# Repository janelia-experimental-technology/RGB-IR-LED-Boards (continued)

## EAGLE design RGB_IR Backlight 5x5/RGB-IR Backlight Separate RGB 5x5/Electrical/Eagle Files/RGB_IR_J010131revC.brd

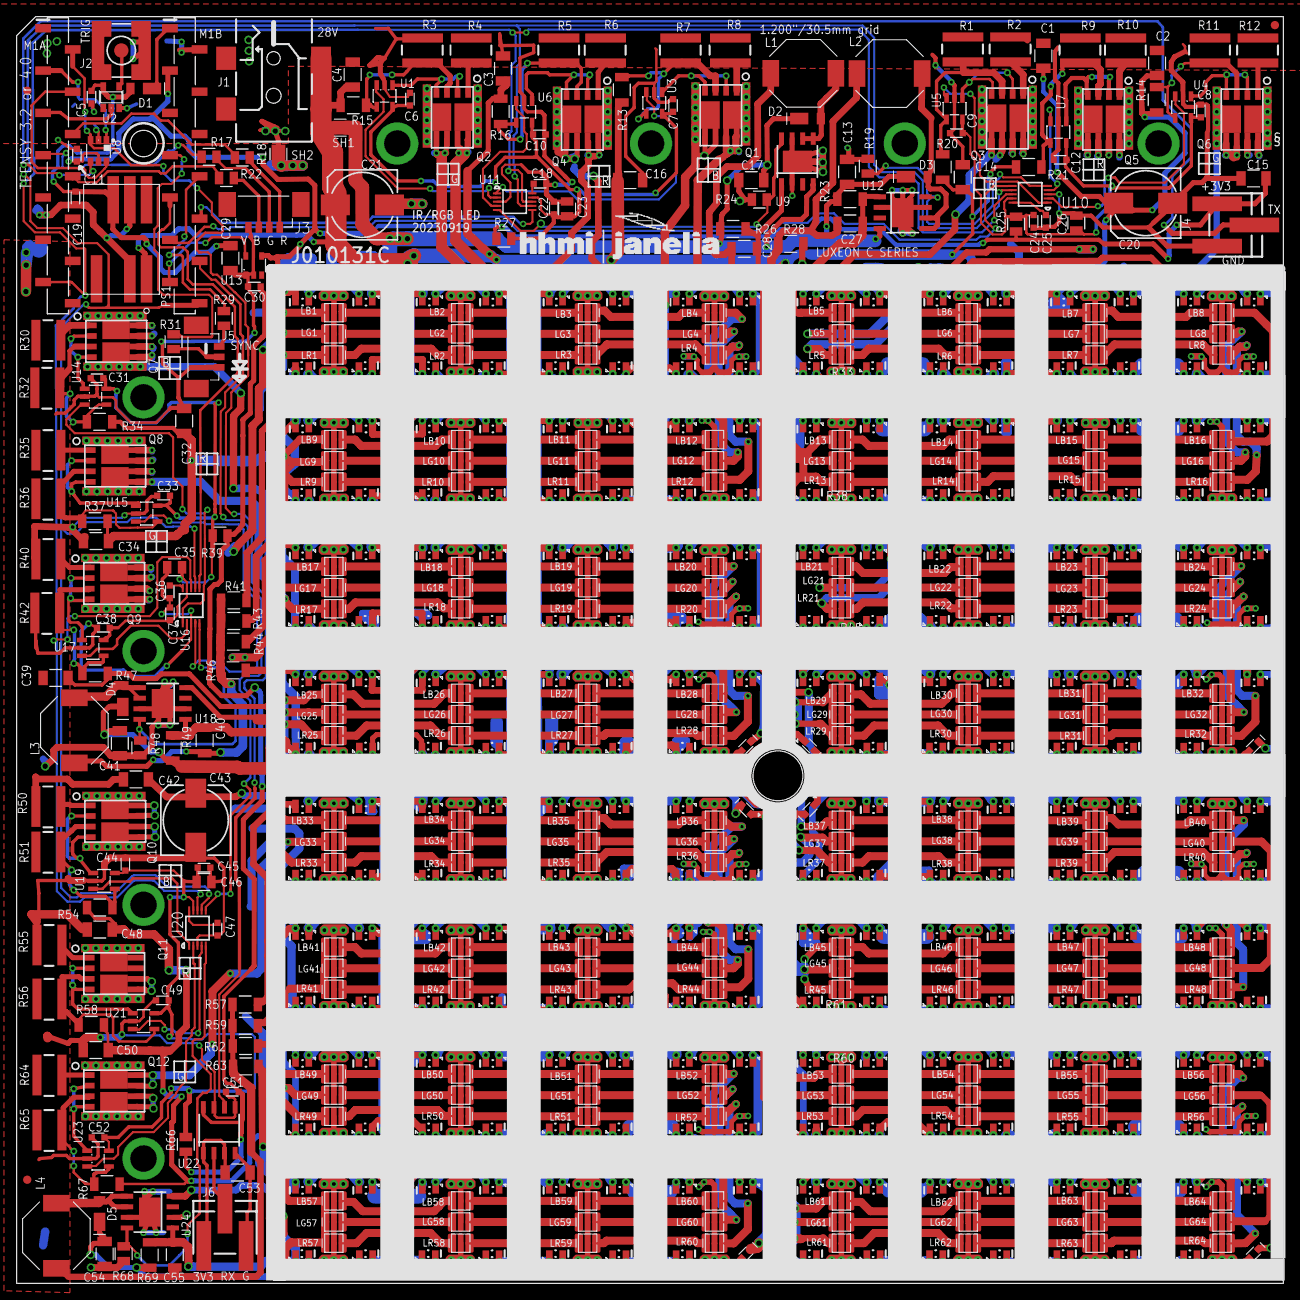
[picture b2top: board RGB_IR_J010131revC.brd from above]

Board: 2 copper layers, 152.1 x 152.1 mm, 696 parts (0 on the bottom side), 617 nets.

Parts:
C1, C2, C3, C4, C13, C14, C16, C17, C32, C34, C39, C41, C42, C48, C50, C54: 10@50; 1210S
C5, C6, C7, C8, C9, C10, C11, C12, C18, C19, C22, C24, C25, C30, C31, C33, C36, C37, C38, C44, C45, C47, C49, C51, C52: 0.1; 0603S
C15, C29, C53: 10; 1210S
C20, C21, C43: 153CLV-0810
C23, C26, C35, C46: 4.7; 0805S
C27, C28, C40, C55: 2.2@50; 1206S
D1, D2, D3, D4, D5: DLFS240L; PWRDI-123
FID1, FID2, FID3, FID4: FIDUCIAL; FIDUCIAL_1MM
IR1, IR129, IR154: SFH4050; LED_SFH4045_HEAT_A
IR2, IR3, IR4, IR5, IR6, IR7, IR8, IR9, IR10, IR11, IR12, IR13, IR14, IR15, IR16, IR17, IR18, IR19, IR20, IR21, IR22, IR23, IR24, IR25, IR26, IR27, IR28, IR29, IR30, IR31, IR32, IR33, IR34, IR35, IR36, IR37, IR38, IR39, IR40, IR41, IR42, IR43, IR44, IR45, IR46, IR47, IR48, IR49, IR50, IR51, IR52, IR53, IR54, IR55, IR56, IR57, IR58, IR59, IR60, IR61, IR62, IR63, IR64, IR65, IR66, IR67, IR68, IR69, IR70, IR71, IR72, IR73, IR74, IR75, IR76, IR77, IR78, IR79, IR80, IR81, IR82, IR83, IR84, IR85, IR86, IR87, IR88, IR89, IR90, IR91, IR92, IR93, IR94, IR95, IR96, IR97, IR98, IR99, IR100, IR101, IR102, IR103, IR104, IR105, IR107, IR108, IR109, IR110, IR111, IR112, IR113, IR114, IR115, IR116, IR118, IR119, IR120, IR121, IR122, IR123, IR125, IR126, IR127, IR130, IR131, IR132, IR133, IR134, IR135, IR138, IR139, IR140, IR141, IR142, IR143, IR144, IR145, IR146, IR147, IR148, IR149, IR150, IR151, IR152, IR153, IR155, IR156, IR157, IR158, IR159, IR160, IR161, IR162, IR163, IR164, IR165, IR166, IR167, IR168, IR169, IR170, IR171, IR172, IR173, IR174, IR175, IR176, IR177, IR178, IR179, IR180, IR181, IR182, IR183, IR184, IR185, IR186, IR187, IR188, IR189, IR190, IR191, IR192, IR193, IR194, IR195, IR196, IR197, IR198, IR199, IR200, IR201, IR202, IR203, IR204, IR205, IR206, IR207, IR208, IR209, IR210, IR211, IR212, IR213, IR214, IR215, IR216, IR217, IR218, IR219, IR220, IR221, IR222, IR223, IR224, IR225, IR226, IR227, IR228, IR229, IR230, IR231, IR232, IR233, IR234, IR235, IR236, IR237, IR238, IR239, IR240, IR241, IR242, IR243, IR244, IR245, IR246, IR247, IR248, IR249, IR250, IR251, IR253, IR254, IR255: SFH4050; LED_SFH4050_HEAT
IR106: SFH4050; LED_SFH4050_HEAT_C
IR117, IR124, IR128, IR136, IR137, IR252, IR256: SFH4050; LED_SFH4050
J1: PJ-002
J2: SMA-SMD
J3: MOLEX_1.25-4
J4, J6: TE-3-SM-V
J5: MOLEX_1.25-3
L1, L2, L3, L4: 68uH/1A; SRU8043
LB1, LB2, LB3, LB4, LB5, LB6, LB7, LB8, LB9, LB10, LB11, LB12, LB13, LB14, LB15, LB16, LB17, LB18, LB19, LB20, LB21, LB22, LB23, LB24, LB25, LB26, LB27, LB28, LB29, LB30, LB31, LB32, LB33, LB34, LB35, LB36, LB37, LB38, LB39, LB40, LB41, LB42, LB43, LB44, LB45, LB46, LB47, LB48, LB49, LB50, LB51, LB52, LB53, LB54, LB55, LB56, LB57, LB58, LB59, LB60, LB61, LB62, LB63, LB64: LED-B; SUNPLUS-LED
LG1, LG2, LG3, LG4, LG5, LG6, LG7, LG8, LG9, LG10, LG11, LG12, LG13, LG14, LG15, LG16, LG17, LG18, LG19, LG20, LG21, LG22, LG23, LG24, LG25, LG26, LG27, LG28, LG29, LG30, LG31, LG32, LG33, LG34, LG35, LG36, LG37, LG38, LG39, LG40, LG41, LG42, LG43, LG44, LG45, LG46, LG47, LG48, LG49, LG50, LG51, LG52, LG53, LG54, LG55, LG56, LG57, LG58, LG59, LG60, LG61, LG62, LG63, LG64: LED-G; SUNPLUS-LED
LR1, LR2, LR3, LR4, LR5, LR6, LR7, LR8, LR9, LR10, LR11, LR12, LR13, LR14, LR15, LR16, LR17, LR18, LR19, LR20, LR21, LR22, LR23, LR24, LR25, LR26, LR27, LR28, LR29, LR30, LR31, LR32, LR33, LR34, LR35, LR36, LR37, LR38, LR39, LR40, LR41, LR42, LR43, LR44, LR45, LR46, LR47, LR48, LR49, LR50, LR51, LR52, LR53, LR54, LR55, LR56, LR57, LR58, LR59, LR60, LR61, LR62, LR63, LR64: LED-R; SUNPLUS-LED
M1A, M1B: SSM-114-S-SV; SAMTEC_SSM-114-S-SV
PS1: DC-DC-TDN-5W
Q1, Q2, Q3, Q4, Q5, Q6, Q7, Q8, Q9, Q10, Q11, Q12: NPN_DUALLFPAK56_BIGHS; LFPAK56_HS2
R1, R2, R3, R4, R5, R6, R7, R8, R9, R10, R11, R12, R30, R32, R35, R36, R40, R42, R50, R51, R55, R56, R64, R65: 4R99; 1812
R13, R14, R15, R16, R20, R21, R34, R37, R47, R54, R58, R67: 49K9; 1206S
R17, R18, R22, R31: 332; 0805S
R19, R24, R48, R68: 4.99K; 0805S
R23, R26, R49, R69: 1R00; 1206S
R25, R27, R39, R66: 4R99; 0805S
R28, R33, R38, R41, R43, R44, R45, R46, R52, R53, R57, R59, R60, R61, R62, R63: 10R0; 1206S
R29: 100; 0805S
SH1, SH2: JUMPER
U1, U3, U4, U5, U6, U7, U14, U15, U17, U19, U21, U23: OPA237; SOT23-5
U2: 74AUC1G17DBV; SOT23-5
U8: 741G3157DBVR; DBV_R-PDSO-G6
U9, U12, U18, U24: AP8802; SOIC8-EP
U10, U11, U16, U20: AD5624R-3; MSOP10
U13: LM26; SOT23-5
U22: ADUM1100; SOIC8
V1, V2, V3, V10, V11: HS; SUNPLUS-VIAS-ONLY
V4, V12: HS; SUNPLUS-TOP-VIAS-ONLY
V5, V6, V7, V9, V13, V14, V15, V17, V18, V19, V21, V22, V23, V25, V26, V27, V29, V30, V31, V33, V34, V35, V37, V38, V39, V41, V42, V43, V45, V46, V47, V49, V50, V51, V53, V54, V55, V57, V58, V59, V61, V62, V63: SUNPLUS-VIAS-ONLY
V8, V16, V20, V24, V28, V32, V36, V40, V44, V48, V52, V56, V60, V64: SUNPLUS-VIAS-ONLYTOPVIAS; SUNPLUS-TOP-VIAS-ONLY

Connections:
3V3I: C53.1, J6.P$3, U22.1, U22.3
3V3LL: C44.1, C45.1, C46.1, C49.1, C52.1, R66.2, U19.5, U20.9, U21.5, U23.5
3V3LR: C6.1, C7.1, C10.1, C22.1, C23.1, R27.2, U1.5, U3.5, U6.5, U11.9
3V3UR: C8.1, C9.1, C12.1, C24.1, C26.1, R25.2, U4.5, U5.5, U7.5, U10.9
+3V3A: C11.1, C15.2, C30.1, C51.1, J4.P$3, M1B.3, R25.1, R27.1, R39.1, R66.1, U8.5, U13.4, U22.8
+3V3UL: C31.1, C33.1, C35.1, C37.1, C38.1, R39.2, U14.5, U15.5, U16.9, U17.5
B1A: LB53.GC, Q1.5, Q1.5A, Q1.5A1, Q1.5B, Q1.5C, Q1.5C1, Q1.5C2, Q1.6, Q1.56, Q1.56A, Q1.56B
B1B: LB37.GC, Q1.7, Q1.8, Q1.8A, Q1.8B, Q1.8C, Q1.8C1, Q1.8C2, Q1.8C3, Q1.78, Q1.78A, Q1.78B
BLLA: LB49.GC, Q10.5, Q10.5A, Q10.5A1, Q10.5B, Q10.5C, Q10.5C1, Q10.5C2, Q10.6, Q10.56, Q10.56A, Q10.56B
BLLB: LB33.GC, Q10.7, Q10.8, Q10.8A, Q10.8B, Q10.8C, Q10.8C1, Q10.8C2, Q10.8C3, Q10.78, Q10.78A, Q10.78B
BLU: M1A.8, R22.2
BLU_LL: U19.3, U20.1
BLU_LR: U3.3, U11.1
BLU_UL: U14.3, U16.1
BLU_UR: U5.3, U10.1
BULA: LB17.GC, Q7.5, Q7.5A, Q7.5A1, Q7.5B, Q7.5C, Q7.5C1, Q7.5C2, Q7.6, Q7.56, Q7.56A, Q7.56B
BULB: LB1.GC, Q7.7, Q7.8, Q7.8A, Q7.8B, Q7.8C, Q7.8C1, Q7.8C2, Q7.8C3, Q7.78, Q7.78A, Q7.78B
DIR: M1A.4, U8.6
G1A: LG53.GC, Q2.5, Q2.5A, Q2.5A1, Q2.5B, Q2.5C, Q2.5C1, Q2.5C2, Q2.6, Q2.56, Q2.56A, Q2.56B
G1B: LG37.GC, Q2.7, Q2.8, Q2.8A, Q2.8B, Q2.8C, Q2.8C1, Q2.8C2, Q2.8C3, Q2.78, Q2.78A, Q2.78B
GLLA: LG49.GC, Q12.5, Q12.5A, Q12.5A1, Q12.5B, Q12.5C, Q12.5C1, Q12.5C2, Q12.6, Q12.56, Q12.56A, Q12.56B
GLLB: LG33.GC, Q12.7, Q12.8, Q12.8A, Q12.8B, Q12.8C, Q12.8C1, Q12.8C2, Q12.8C3, Q12.78, Q12.78A, Q12.78B
GNDI: C53.2, J6.P$1, U22.4
GRN: M1A.7, R17.2
GRN_LL: U20.2, U23.3
GRN_LR: U1.3, U11.2
GRN_UL: U16.2, U17.3
GRN_UR: U4.3, U10.2
GULA_1: LG17.GC, Q9.5, Q9.5A, Q9.5A1, Q9.5B, Q9.5C, Q9.5C1, Q9.5C2, Q9.6, Q9.56, Q9.56A, Q9.56B
GULB_A: LG1.GC, Q9.7, Q9.8, Q9.8A, Q9.8B, Q9.8C, Q9.8C1, Q9.8C2, Q9.8C3, Q9.78, Q9.78A, Q9.78B
IGND: C13.2, C17.2, C21.-, C41.2, C54.2, R19.1, R24.1, R48.1, R68.1, SH2.2, U9.2, U9.7, U9.EP, U12.2, U12.7, U12.EP, U18.2, U18.7, U18.EP, U24.2, U24.7, U24.EP
IR_DRV_LL: C55.1, IR145.A, IR145.A1, IR177.A, IR177.A1, IR209.A, IR209.A1, IR241.A, IR241.A1, R69.1, U24.1
IR_DRV_LR: C28.1, IR153.A, IR153.A1, IR185.A, IR185.A1, IR217.A, IR217.A1, IR245.A, IR245.A1, R26.1, U9.1
IR_DRV_UL: C40.1, IR17.A, IR17.A1, IR49.A, IR49.A1, IR81.A, IR81.A1, IR113.A, IR113.A1, R49.1, U18.1
IR_DRV_UR: C27.1, IR25.A, IR25.A1, IR57.A, IR57.A1, IR89.A, IR89.A1, IR117.A, R23.1, U12.1
IR_LL: R68.2, U20.5, U24.8
IR_LR: R24.2, U9.8, U11.5
IR_RET_UL: C40.2, L3.1, R41.2, R43.2, R44.2, R46.2
IR_RET_UL1: C55.2, L4.1, R57.2, R59.2, R62.2, R63.2
IR_RET_UL2: C27.2, L2.1, R28.2, R33.2, R38.2, R45.2
IR_RET_UL3: C28.2, L1.1, R52.2, R53.2, R60.2, R61.2
IR_UL: R48.2, U16.5, U18.8
IR_UR: R19.2, U10.5, U12.8
ISO-5: C5.1, C19.1, C29.1, D1.A, PS1.7, U2.5
LED: M1B.7, R31.2
LGND: C1.2, C2.2, C3.2, C4.2, C5.2, C6.2, C7.2, C8.2, C9.2, C10.2, C11.2, C12.2, C14.2, C15.1, C16.2, C18.2, C19.2, C20.-, C22.2, C23.2, C24.2, C25.2, C26.2, C29.2, C30.2, C31.2, C32.2, C33.2, C34.2, C35.2, C36.2, C37.2, C38.2, C39.2, C42.2, C43.-, C44.2, C45.2, C46.2, C47.2, C48.2, C49.2, C50.2, C51.2, C52.2, J1.2, J2.2@1, J2.2@2, J2.2@3, J2.2@4, J2.2@5, J2.2@6, J3.4, J4.P$1, J5.3, M1A.1, M1B.2, PS1.2, PS1.6, R1.1, R2.1, R3.1, R4.1, R5.1, R6.1, R7.1, R8.1, R9.1, R10.1, R11.1, R12.1, R30.1, R32.1, R35.1, R36.1, R40.1, R42.1, R50.1, R51.1, R55.1, R56.1, R64.1, R65.1, SH2.1, U1.2, U2.3, U3.2, U4.2, U5.2, U6.2, U7.2, U8.2, U10.3, U11.3, U13.1, U13.2, U14.2, U15.2, U16.3, U17.2, U19.2, U20.3, U21.2, U22.5, U22.7, U23.2
LL_EN: M1B.12, U20.6
LR_EN: M1B.10, U11.6
MOSI: M1A.13, U10.8, U11.8, U16.8, U20.8
unnamed: IR7.A, IR7.A1, IR8.C, IR8.C1
unnamed: IR6.A, IR6.A1, IR7.C, IR7.C1
unnamed: IR71.A, IR71.A1, IR72.C, IR72.C1
unnamed: IR70.A, IR70.A1, IR71.C, IR71.C1
unnamed: IR69.A, IR69.A1, IR70.C, IR70.C1
unnamed: IR67.A, IR67.A1, IR68.C, IR68.C1
unnamed: IR66.A, IR66.A1, IR67.C, IR67.C1
unnamed: IR65.A, IR65.A1, IR66.C, IR66.C1
unnamed: IR5.A, IR5.A1, IR6.C, IR6.C1
unnamed: IR3.A, IR3.A1, IR4.C, IR4.C1
unnamed: IR2.A, IR2.A1, IR3.C, IR3.C1
unnamed: IR1.A, IR1.A1, IR2.C, IR2.C1
unnamed: IR17.C, IR17.C1, IR18.A, IR18.A1
unnamed: IR81.C, IR81.C1, IR82.A, IR82.A1
unnamed: IR18.C, IR18.C1, IR19.A, IR19.A1
unnamed: IR82.C, IR82.C1, IR83.A, IR83.A1
unnamed: IR83.C, IR83.C1, IR84.A, IR84.A1
unnamed: IR68.A, IR68.A1, IR69.C, IR69.C1
unnamed: IR103.A, IR103.A1, IR104.C, IR104.C1
unnamed: IR102.A, IR102.A1, IR103.C, IR103.C1
unnamed: IR101.A, IR101.A1, IR102.C, IR102.C1
unnamed: IR100.A, IR100.A1, IR101.C, IR101.C1
unnamed: IR99.A, IR99.A1, IR100.C, IR100.C1
unnamed: IR19.C, IR19.C1, IR20.A, IR20.A1
unnamed: IR4.A, IR4.A1, IR5.C, IR5.C1
unnamed: IR39.A, IR39.A1, IR40.C, IR40.C1
unnamed: IR38.A, IR38.A1, IR39.C, IR39.C1
unnamed: IR37.A, IR37.A1, IR38.C, IR38.C1
unnamed: IR98.A, IR98.A1, IR99.C, IR99.C1
unnamed: IR36.A, IR36.A1, IR37.C, IR37.C1
unnamed: IR35.A, IR35.A1, IR36.C, IR36.C1
unnamed: IR97.A, IR97.A1, IR98.C, IR98.C1
unnamed: IR85.C, IR85.C1, IR86.A, IR86.A1
unnamed: IR86.C, IR86.C1, IR87.A, IR87.A1
unnamed: IR34.A, IR34.A1, IR35.C, IR35.C1
unnamed: IR87.C, IR87.C1, IR88.A, IR88.A1
unnamed: IR33.A, IR33.A1, IR34.C, IR34.C1
unnamed: IR21.C, IR21.C1, IR22.A, IR22.A1
unnamed: IR22.C, IR22.C1, IR23.A, IR23.A1
unnamed: IR23.C, IR23.C1, IR24.A, IR24.A1
unnamed: IR49.C, IR49.C1, IR50.A, IR50.A1
unnamed: IR50.C, IR50.C1, IR51.A, IR51.A1
unnamed: IR51.C, IR51.C1, IR52.A, IR52.A1
unnamed: IR53.C, IR53.C1, IR54.A, IR54.A1
unnamed: IR54.C, IR54.C1, IR55.A, IR55.A1
unnamed: IR55.C, IR55.C1, IR56.A, IR56.A1
unnamed: IR113.C, IR113.C1, IR114.A, IR114.A1
unnamed: IR20.C, IR20.C1, IR21.A, IR21.A1
unnamed: IR114.C, IR114.C1, IR115.A, IR115.A1
unnamed: IR8.A, IR8.A1, IR24.C, IR24.C1
unnamed: IR52.C, IR52.C1, IR53.A, IR53.A1
unnamed: IR115.C, IR115.C1, IR121.A, IR121.A1
unnamed: IR1.C, R41.1
unnamed: IR40.A, IR40.A1, IR56.C, IR56.C1
unnamed: IR33.C, IR33.C1, R43.1
unnamed: LG9.GC, LG10.GA
unnamed: LR9.GC, LR10.GA
unnamed: IR65.C, IR65.C1, R44.1
unnamed: IR135.A, IR135.A1, IR136.C
unnamed: LB9.GC, LB10.GA
unnamed: IR116.C, IR116.C1, IR122.A, IR122.A1
unnamed: IR134.A, IR134.A1, IR135.C, IR135.C1
unnamed: LG10.GC, LG11.GA
unnamed: IR122.C, IR122.C1, IR123.A, IR123.A1
unnamed: IR123.C, IR123.C1, IR124.A
unnamed: Q8.3, R36.2, R37.1, U15.4
unnamed: D4.A, L3.2, U18.5, U18.6
unnamed: IR84.C, IR84.C1, IR85.A, IR85.A1
unnamed: LR10.GC, LR11.GA
unnamed: IR72.A, IR72.A1, IR88.C, IR88.C1
unnamed: C36.1, U16.10
unnamed: IR116.A, IR116.A1, IR121.C, IR121.C1
unnamed: LB10.GC, LB11.GA
unnamed: LG11.GC, LG12.GA
unnamed: IR104.A, IR104.A1, IR124.C
unnamed: IR133.A, IR133.A1, IR134.C, IR134.C1
unnamed: LR11.GC, LR12.GA
unnamed: IR97.C, IR97.C1, R46.1
unnamed: Q9.3, R42.2, R47.1, U17.4
unnamed: LB11.GC, LB12.GA
unnamed: LG4.GA, LG12.GC
unnamed: Q8.1, R35.2
unnamed: LR4.GA, LR12.GC
unnamed: Q8.2, Q8.4, U15.1
unnamed: LB4.GA, LB12.GC
unnamed: LB2.GA, LB3.GC
unnamed: LR2.GA, LR3.GC
unnamed: LG2.GA, LG3.GC
unnamed: LB1.GA, LB2.GC
unnamed: C47.1, U20.10
unnamed: LR1.GA, LR2.GC
unnamed: LG1.GA, LG2.GC
unnamed: LG3.GA, LG4.GC
unnamed: LR3.GA, LR4.GC
unnamed: LB3.GA, LB4.GC
unnamed: C25.1, U10.10
unnamed: Q9.2, Q9.4, U17.1
unnamed: C18.1, U11.10
unnamed: LG25.GC, LG26.GA
unnamed: LR25.GC, LR26.GA
unnamed: LB25.GC, LB26.GA
unnamed: LG26.GC, LG27.GA
unnamed: LR26.GC, LR27.GA
unnamed: LB26.GC, LB27.GA
unnamed: LG27.GC, LG28.GA
unnamed: LR27.GC, LR28.GA
unnamed: LB27.GC, LB28.GA
unnamed: LG20.GA, LG28.GC
unnamed: LR20.GA, LR28.GC
unnamed: LB20.GA, LB28.GC
unnamed: LG19.GA, LG20.GC
unnamed: LR19.GA, LR20.GC
unnamed: LB19.GA, LB20.GC
unnamed: LG18.GA, LG19.GC
unnamed: LR18.GA, LR19.GC
unnamed: LB18.GA, LB19.GC
unnamed: LG17.GA, LG18.GC
unnamed: LR17.GA, LR18.GC
unnamed: LB17.GA, LB18.GC
unnamed: Q7.2, Q7.4, U14.1
unnamed: J3.3, R22.1
unnamed: IR131.A, IR131.A1, IR132.C, IR132.C1
unnamed: Q7.1, R30.2
unnamed: J2.1, U2.4
unnamed: Q9.1, R40.2
unnamed: IR130.A, IR130.A1, IR131.C, IR131.C1
unnamed: IR129.A, IR129.A1, IR130.C, IR130.C1
unnamed: IR145.C, IR145.C1, IR146.A, IR146.A1
unnamed: IR146.C, IR146.C1, IR147.A, IR147.A1
unnamed: IR147.C, IR147.C1, IR148.A, IR148.A1
unnamed: IR132.A, IR132.A1, IR133.C, IR133.C1
unnamed: IR167.A, IR167.A1, IR168.C, IR168.C1
unnamed: IR166.A, IR166.A1, IR167.C, IR167.C1
unnamed: IR165.A, IR165.A1, IR166.C, IR166.C1
unnamed: IR164.A, IR164.A1, IR165.C, IR165.C1
unnamed: IR163.A, IR163.A1, IR164.C, IR164.C1
unnamed: IR162.A, IR162.A1, IR163.C, IR163.C1
unnamed: IR161.A, IR161.A1, IR162.C, IR162.C1
unnamed: IR149.C, IR149.C1, IR150.A, IR150.A1
unnamed: IR150.C, IR150.C1, IR151.A, IR151.A1
unnamed: IR151.C, IR151.C1, IR152.A, IR152.A1
unnamed: IR177.C, IR177.C1, IR178.A, IR178.A1
unnamed: IR178.C, IR178.C1, IR179.A, IR179.A1
unnamed: IR179.C, IR179.C1, IR180.A, IR180.A1
unnamed: IR181.C, IR181.C1, IR182.A, IR182.A1
unnamed: IR182.C, IR182.C1, IR183.A, IR183.A1
unnamed: IR183.C, IR183.C1, IR184.A, IR184.A1
unnamed: IR148.C, IR148.C1, IR149.A, IR149.A1
unnamed: IR136.A, IR152.C, IR152.C1
unnamed: IR180.C, IR180.C1, IR181.A, IR181.A1
unnamed: IR168.A, IR168.A1, IR184.C, IR184.C1
unnamed: IR129.C, R57.1
unnamed: IR161.C, IR161.C1, R59.1
unnamed: IR199.A, IR199.A1, IR200.C, IR200.C1
unnamed: IR198.A, IR198.A1, IR199.C, IR199.C1
unnamed: IR197.A, IR197.A1, IR198.C, IR198.C1
unnamed: IR195.A, IR195.A1, IR196.C, IR196.C1
unnamed: IR194.A, IR194.A1, IR195.C, IR195.C1
unnamed: IR193.A, IR193.A1, IR194.C, IR194.C1
unnamed: IR209.C, IR209.C1, IR210.A, IR210.A1
unnamed: IR210.C, IR210.C1, IR211.A, IR211.A1
unnamed: IR211.C, IR211.C1, IR212.A, IR212.A1
unnamed: IR196.A, IR196.A1, IR197.C, IR197.C1
unnamed: IR231.A, IR231.A1, IR232.C, IR232.C1
unnamed: IR230.A, IR230.A1, IR231.C, IR231.C1
unnamed: IR229.A, IR229.A1, IR230.C, IR230.C1
unnamed: IR228.A, IR228.A1, IR229.C, IR229.C1
unnamed: IR227.A, IR227.A1, IR228.C, IR228.C1
unnamed: IR226.A, IR226.A1, IR227.C, IR227.C1
unnamed: IR225.A, IR225.A1, IR226.C, IR226.C1
unnamed: IR213.C, IR213.C1, IR214.A, IR214.A1
unnamed: IR214.C, IR214.C1, IR215.A, IR215.A1
unnamed: IR215.C, IR215.C1, IR216.A, IR216.A1
unnamed: IR241.C, IR241.C1, IR242.A, IR242.A1
unnamed: IR242.C, IR242.C1, IR243.A, IR243.A1
unnamed: IR243.C, IR243.C1, IR249.A, IR249.A1
unnamed: IR244.C, IR244.C1, IR250.A, IR250.A1
unnamed: IR250.C, IR250.C1, IR251.A, IR251.A1
unnamed: IR251.C, IR251.C1, IR252.A
unnamed: IR212.C, IR212.C1, IR213.A, IR213.A1
unnamed: IR200.A, IR200.A1, IR216.C, IR216.C1
unnamed: IR244.A, IR244.A1, IR249.C, IR249.C1
unnamed: IR232.A, IR232.A1, IR252.C
unnamed: IR193.C, IR193.C1, R62.1
unnamed: IR225.C, IR225.C1, R63.1
unnamed: Q10.3, R51.2, R54.1, U19.4
unnamed: D5.A, L4.2, U24.5, U24.6
unnamed: Q11.3, R56.2, R58.1, U21.4
unnamed: Q11.2, Q11.4, U21.1
unnamed: LG41.GC, LG42.GA
unnamed: LR41.GC, LR42.GA
unnamed: LB41.GC, LB42.GA
unnamed: LG42.GC, LG43.GA
unnamed: LR42.GC, LR43.GA
unnamed: LB42.GC, LB43.GA
unnamed: LG43.GC, LG44.GA
unnamed: LR43.GC, LR44.GA
unnamed: LB43.GC, LB44.GA
unnamed: LG36.GA, LG44.GC
unnamed: LR36.GA, LR44.GC
unnamed: LG57.GC, LG58.GA
unnamed: Q7.3, R32.2, R34.1, U14.4
unnamed: LR57.GC, LR58.GA
unnamed: LB57.GC, LB58.GA
unnamed: LG58.GC, LG59.GA
unnamed: LR58.GC, LR59.GA
unnamed: LB58.GC, LB59.GA
unnamed: LG59.GC, LG60.GA
unnamed: LR59.GC, LR60.GA
unnamed: LB59.GC, LB60.GA
unnamed: LG52.GA, LG60.GC
unnamed: J3.2, R17.1
unnamed: Q12.3, R65.2, R67.1, U23.4
unnamed: Q12.2, Q12.4, U23.1
unnamed: J3.1, R18.1
unnamed: LR52.GA, LR60.GC
unnamed: LB52.GA, LB60.GC
unnamed: LB36.GA, LB44.GC
unnamed: LB33.GA, LB34.GC
unnamed: LR33.GA, LR34.GC
unnamed: LG33.GA, LG34.GC
unnamed: LB34.GA, LB35.GC
unnamed: LR34.GA, LR35.GC
unnamed: LG34.GA, LG35.GC
unnamed: LG35.GA, LG36.GC
unnamed: LR35.GA, LR36.GC
unnamed: LB35.GA, LB36.GC
unnamed: LG51.GA, LG52.GC
unnamed: LR51.GA, LR52.GC
unnamed: LB51.GA, LB52.GC
unnamed: LG50.GA, LG51.GC
unnamed: LR50.GA, LR51.GC
unnamed: LB50.GA, LB51.GC
unnamed: LG49.GA, LG50.GC
unnamed: LR49.GA, LR50.GC
unnamed: LB49.GA, LB50.GC
unnamed: Q10.2, Q10.4, U19.1
unnamed: LB9.T, LG9.T, LR9.T, V9.T1, V9.T2, V9.T3, V9.T4, V9.T5, V9.T6
unnamed: Q10.1, R50.2
unnamed: Q11.1, R55.2
unnamed: LG13.GC, LG14.GA
unnamed: LR13.GC, LR14.GA
unnamed: Q12.1, R64.2
unnamed: LG45.GC, LG46.GA
unnamed: IR15.A, IR15.A1, IR16.C, IR16.C1
unnamed: IR14.A, IR14.A1, IR15.C, IR15.C1
unnamed: IR13.A, IR13.A1, IR14.C, IR14.C1
unnamed: IR11.A, IR11.A1, IR12.C, IR12.C1
unnamed: IR10.A, IR10.A1, IR11.C, IR11.C1
unnamed: IR9.A, IR9.A1, IR10.C, IR10.C1
unnamed: IR25.C, IR25.C1, IR26.A, IR26.A1
unnamed: IR26.C, IR26.C1, IR27.A, IR27.A1
unnamed: IR27.C, IR27.C1, IR28.A, IR28.A1
unnamed: IR12.A, IR12.A1, IR13.C, IR13.C1
unnamed: IR47.A, IR47.A1, IR48.C, IR48.C1
unnamed: IR46.A, IR46.A1, IR47.C, IR47.C1
unnamed: IR45.A, IR45.A1, IR46.C, IR46.C1
unnamed: IR44.A, IR44.A1, IR45.C, IR45.C1
unnamed: IR43.A, IR43.A1, IR44.C, IR44.C1
unnamed: IR42.A, IR42.A1, IR43.C, IR43.C1
unnamed: IR41.A, IR41.A1, IR42.C, IR42.C1
unnamed: IR29.C, IR29.C1, IR30.A, IR30.A1
unnamed: IR30.C, IR30.C1, IR31.A, IR31.A1
unnamed: IR31.C, IR31.C1, IR32.A, IR32.A1
unnamed: IR57.C, IR57.C1, IR58.A, IR58.A1
unnamed: IR58.C, IR58.C1, IR59.A, IR59.A1
unnamed: IR59.C, IR59.C1, IR60.A, IR60.A1
unnamed: IR61.C, IR61.C1, IR62.A, IR62.A1
unnamed: IR62.C, IR62.C1, IR63.A, IR63.A1
unnamed: IR63.C, IR63.C1, IR64.A, IR64.A1
unnamed: IR28.C, IR28.C1, IR29.A, IR29.A1
unnamed: IR16.A, IR16.A1, IR32.C, IR32.C1
unnamed: IR60.C, IR60.C1, IR61.A, IR61.A1
unnamed: IR48.A, IR48.A1, IR64.C, IR64.C1
unnamed: IR9.C, IR9.C1, R28.1
unnamed: IR41.C, IR41.C1, R33.1
unnamed: IR79.A, IR79.A1, IR80.C, IR80.C1
unnamed: IR78.A, IR78.A1, IR79.C, IR79.C1
unnamed: IR77.A, IR77.A1, IR78.C, IR78.C1
unnamed: IR75.A, IR75.A1, IR76.C, IR76.C1
unnamed: IR74.A, IR74.A1, IR75.C, IR75.C1
unnamed: IR73.A, IR73.A1, IR74.C, IR74.C1
unnamed: IR89.C, IR89.C1, IR90.A, IR90.A1
unnamed: IR90.C, IR90.C1, IR91.A, IR91.A1
unnamed: IR91.C, IR91.C1, IR92.A, IR92.A1
unnamed: IR76.A, IR76.A1, IR77.C, IR77.C1
unnamed: IR111.A, IR111.A1, IR112.C, IR112.C1
unnamed: IR110.A, IR110.A1, IR111.C, IR111.C1
unnamed: IR109.A, IR109.A1, IR110.C, IR110.C1
unnamed: IR108.A, IR108.A1, IR109.C, IR109.C1
unnamed: IR107.A, IR107.A1, IR108.C, IR108.C1
unnamed: IR106.A, IR107.C, IR107.C1
unnamed: IR105.A, IR105.A1, IR106.C, IR106.C1
unnamed: IR93.C, IR93.C1, IR94.A, IR94.A1
unnamed: IR94.C, IR94.C1, IR95.A, IR95.A1
unnamed: IR95.C, IR95.C1, IR96.A, IR96.A1
unnamed: IR117.C, IR118.A, IR118.A1
unnamed: IR118.C, IR118.C1, IR119.A, IR119.A1
unnamed: IR119.C, IR119.C1, IR125.A, IR125.A1
unnamed: IR120.C, IR120.C1, IR126.A, IR126.A1
unnamed: IR126.C, IR126.C1, IR127.A, IR127.A1
unnamed: IR127.C, IR127.C1, IR128.A
unnamed: IR92.C, IR92.C1, IR93.A, IR93.A1
unnamed: IR80.A, IR80.A1, IR96.C, IR96.C1
unnamed: IR120.A, IR120.A1, IR125.C, IR125.C1
unnamed: IR112.A, IR112.A1, IR128.C
unnamed: IR73.C, IR73.C1, R38.1
unnamed: IR105.C, IR105.C1, R45.1
unnamed: Q6.3, R11.2, R14.1, U4.4
unnamed: D3.A, L2.2, U12.5, U12.6
unnamed: Q5.3, R9.2, R21.1, U7.4
unnamed: Q5.2, Q5.4, U7.1
unnamed: LB13.GC, LB14.GA
unnamed: LG14.GC, LG15.GA
unnamed: LR14.GC, LR15.GA
unnamed: LB14.GC, LB15.GA
unnamed: LG15.GC, LG16.GA
unnamed: LR15.GC, LR16.GA
unnamed: LB15.GC, LB16.GA
unnamed: LG8.GA, LG16.GC
unnamed: LR8.GA, LR16.GC
unnamed: LG29.GC, LG30.GA
unnamed: LR29.GC, LR30.GA
unnamed: LB10.T, LG10.T, LR10.T, V10.T1, V10.T2, V10.T3, V10.T4, V10.T5, V10.T6
unnamed: LB29.GC, LB30.GA
unnamed: LG30.GC, LG31.GA
unnamed: LR30.GC, LR31.GA
unnamed: LB30.GC, LB31.GA
unnamed: LG31.GC, LG32.GA
unnamed: LR31.GC, LR32.GA
unnamed: LB31.GC, LB32.GA
unnamed: LG24.GA, LG32.GC
unnamed: LR24.GA, LR32.GC
unnamed: LB11.T, LG11.T, LR11.T, V11.T1, V11.T2, V11.T3, V11.T4, V11.T5, V11.T6
unnamed: Q3.3, R1.2, R20.1, U5.4
unnamed: Q3.2, Q3.4, U5.1
unnamed: LB1.T, LG1.T, LR1.T, V1.T1, V1.T2, V1.T3, V1.T4, V1.T5, V1.T6
unnamed: LB24.GA, LB32.GC
unnamed: LB8.GA, LB16.GC
unnamed: LB5.GA, LB6.GC
unnamed: LR5.GA, LR6.GC
unnamed: LG5.GA, LG6.GC
unnamed: LB6.GA, LB7.GC
unnamed: LR6.GA, LR7.GC
unnamed: LG6.GA, LG7.GC
unnamed: LG7.GA, LG8.GC
unnamed: LR7.GA, LR8.GC
unnamed: LB7.GA, LB8.GC
unnamed: LG23.GA, LG24.GC
unnamed: LR23.GA, LR24.GC
unnamed: LB23.GA, LB24.GC
unnamed: LG22.GA, LG23.GC
unnamed: LR22.GA, LR23.GC
unnamed: LB22.GA, LB23.GC
unnamed: LG21.GA, LG22.GC
unnamed: LR21.GA, LR22.GC
unnamed: LB21.GA, LB22.GC
unnamed: Q6.2, Q6.4, U4.1
unnamed: LB4.T, LG4.T, LR4.T, V4.T1, V4.T2, V4.T3
unnamed: Q6.1, R12.2
unnamed: Q5.1, R10.2
unnamed: J5.2, R31.1
unnamed: LB25.T, LG25.T, LR25.T, V25.T1, V25.T2, V25.T3, V25.T4, V25.T5, V25.T6
unnamed: Q3.1, R2.2
unnamed: LB27.T, LG27.T, LR27.T, V27.T1, V27.T2, V27.T3, V27.T4, V27.T5, V27.T6
unnamed: IR143.A, IR143.A1, IR144.C, IR144.C1
unnamed: IR142.A, IR142.A1, IR143.C, IR143.C1
unnamed: IR141.A, IR141.A1, IR142.C, IR142.C1
unnamed: IR139.A, IR139.A1, IR140.C, IR140.C1
unnamed: IR138.A, IR138.A1, IR139.C, IR139.C1
unnamed: IR137.A, IR138.C, IR138.C1
unnamed: IR153.C, IR153.C1, IR154.A, IR154.A1
unnamed: IR154.C, IR155.A, IR155.A1
unnamed: IR155.C, IR155.C1, IR156.A, IR156.A1
unnamed: IR140.A, IR140.A1, IR141.C, IR141.C1
unnamed: IR175.A, IR175.A1, IR176.C, IR176.C1
unnamed: IR174.A, IR174.A1, IR175.C, IR175.C1
unnamed: IR173.A, IR173.A1, IR174.C, IR174.C1
unnamed: IR172.A, IR172.A1, IR173.C, IR173.C1
unnamed: IR171.A, IR171.A1, IR172.C, IR172.C1
unnamed: IR170.A, IR170.A1, IR171.C, IR171.C1
unnamed: IR169.A, IR169.A1, IR170.C, IR170.C1
unnamed: IR157.C, IR157.C1, IR158.A, IR158.A1
unnamed: IR158.C, IR158.C1, IR159.A, IR159.A1
unnamed: IR159.C, IR159.C1, IR160.A, IR160.A1
unnamed: IR185.C, IR185.C1, IR186.A, IR186.A1
unnamed: IR186.C, IR186.C1, IR187.A, IR187.A1
unnamed: IR187.C, IR187.C1, IR188.A, IR188.A1
unnamed: IR189.C, IR189.C1, IR190.A, IR190.A1
unnamed: IR190.C, IR190.C1, IR191.A, IR191.A1
unnamed: IR191.C, IR191.C1, IR192.A, IR192.A1
unnamed: IR156.C, IR156.C1, IR157.A, IR157.A1
unnamed: IR144.A, IR144.A1, IR160.C, IR160.C1
unnamed: IR188.C, IR188.C1, IR189.A, IR189.A1
unnamed: IR176.A, IR176.A1, IR192.C, IR192.C1
unnamed: IR137.C, R52.1
unnamed: IR169.C, IR169.C1, R53.1
unnamed: IR207.A, IR207.A1, IR208.C, IR208.C1
unnamed: IR206.A, IR206.A1, IR207.C, IR207.C1
unnamed: IR205.A, IR205.A1, IR206.C, IR206.C1
unnamed: IR203.A, IR203.A1, IR204.C, IR204.C1
unnamed: IR202.A, IR202.A1, IR203.C, IR203.C1
unnamed: IR201.A, IR201.A1, IR202.C, IR202.C1
unnamed: IR217.C, IR217.C1, IR218.A, IR218.A1
unnamed: IR218.C, IR218.C1, IR219.A, IR219.A1
unnamed: IR219.C, IR219.C1, IR220.A, IR220.A1
unnamed: IR204.A, IR204.A1, IR205.C, IR205.C1
unnamed: IR239.A, IR239.A1, IR240.C, IR240.C1
unnamed: IR238.A, IR238.A1, IR239.C, IR239.C1
unnamed: IR237.A, IR237.A1, IR238.C, IR238.C1
unnamed: IR236.A, IR236.A1, IR237.C, IR237.C1
unnamed: IR235.A, IR235.A1, IR236.C, IR236.C1
unnamed: IR234.A, IR234.A1, IR235.C, IR235.C1
unnamed: IR233.A, IR233.A1, IR234.C, IR234.C1
unnamed: IR221.C, IR221.C1, IR222.A, IR222.A1
unnamed: IR222.C, IR222.C1, IR223.A, IR223.A1
unnamed: IR223.C, IR223.C1, IR224.A, IR224.A1
unnamed: IR245.C, IR245.C1, IR246.A, IR246.A1
unnamed: IR246.C, IR246.C1, IR247.A, IR247.A1
unnamed: IR247.C, IR247.C1, IR253.A, IR253.A1
unnamed: IR248.C, IR248.C1, IR254.A, IR254.A1
unnamed: IR254.C, IR254.C1, IR255.A, IR255.A1
unnamed: IR255.C, IR255.C1, IR256.A
unnamed: IR220.C, IR220.C1, IR221.A, IR221.A1
unnamed: IR208.A, IR208.A1, IR224.C, IR224.C1
unnamed: IR248.A, IR248.A1, IR253.C, IR253.C1
unnamed: IR240.A, IR240.A1, IR256.C
unnamed: IR201.C, IR201.C1, R61.1
unnamed: IR233.C, IR233.C1, R60.1
unnamed: Q1.3, R7.2, R13.1, U3.4
unnamed: D2.A, L1.2, U9.5, U9.6
unnamed: Q4.3, R5.2, R16.1, U6.4
unnamed: Q4.2, Q4.4, U6.1
unnamed: LR45.GC, LR46.GA
unnamed: LB45.GC, LB46.GA
unnamed: LG46.GC, LG47.GA
unnamed: LR46.GC, LR47.GA
unnamed: LB46.GC, LB47.GA
unnamed: LG47.GC, LG48.GA
unnamed: LR47.GC, LR48.GA
unnamed: LB47.GC, LB48.GA
unnamed: LG40.GA, LG48.GC
unnamed: LR40.GA, LR48.GC
unnamed: LG61.GC, LG62.GA
unnamed: LB26.T, LG26.T, LR26.T, V26.T1, V26.T2, V26.T3, V26.T4, V26.T5, V26.T6
unnamed: LR61.GC, LR62.GA
unnamed: LB61.GC, LB62.GA
unnamed: LG62.GC, LG63.GA
unnamed: LR62.GC, LR63.GA
unnamed: LB62.GC, LB63.GA
unnamed: LG63.GC, LG64.GA
unnamed: LR63.GC, LR64.GA
unnamed: LB63.GC, LB64.GA
unnamed: LG56.GA, LG64.GC
unnamed: LB20.T, LG20.T, LR20.T, V20.T1, V20.T2, V20.T3
unnamed: Q2.3, R3.2, R15.1, U1.4
unnamed: Q2.2, Q2.4, U1.1
unnamed: LB19.T, LG19.T, LR19.T, V19.T1, V19.T2, V19.T3, V19.T4, V19.T5, V19.T6
unnamed: LR56.GA, LR64.GC
unnamed: LB56.GA, LB64.GC
unnamed: LB40.GA, LB48.GC
unnamed: LB37.GA, LB38.GC
unnamed: LR37.GA, LR38.GC
unnamed: LG37.GA, LG38.GC
unnamed: LB38.GA, LB39.GC
unnamed: LR38.GA, LR39.GC
unnamed: LG38.GA, LG39.GC
unnamed: LG39.GA, LG40.GC
unnamed: LR39.GA, LR40.GC
unnamed: LB39.GA, LB40.GC
unnamed: LG55.GA, LG56.GC
unnamed: LR55.GA, LR56.GC
unnamed: LB55.GA, LB56.GC
unnamed: LG54.GA, LG55.GC
unnamed: LR54.GA, LR55.GC
unnamed: LB54.GA, LB55.GC
unnamed: LG53.GA, LG54.GC
unnamed: LR53.GA, LR54.GC
unnamed: LB53.GA, LB54.GC
unnamed: Q1.2, Q1.4, U3.1
unnamed: LB17.T, LG17.T, LR17.T, V17.T1, V17.T2, V17.T3, V17.T4, V17.T5, V17.T6
unnamed: Q1.1, R8.2
unnamed: Q4.1, R6.2
unnamed: LB41.T, LG41.T, LR41.T, V41.T1, V41.T2, V41.T3, V41.T4, V41.T5, V41.T6
unnamed: Q2.1, R4.2
unnamed: LB42.T, LG42.T, LR42.T, V42.T1, V42.T2, V42.T3, V42.T4, V42.T5, V42.T6
unnamed: LB43.T, LG43.T, LR43.T, V43.T1, V43.T2, V43.T3, V43.T4, V43.T5, V43.T6
unnamed: LB33.T, LG33.T, LR33.T, V33.T1, V33.T2, V33.T3, V33.T4, V33.T5, V33.T6
unnamed: LB36.T, LG36.T, LR36.T, V36.T1, V36.T2, V36.T3
unnamed: LB57.T, LG57.T, LR57.T, V57.T1, V57.T2, V57.T3, V57.T4, V57.T5, V57.T6
unnamed: LB58.T, LG58.T, LR58.T, V58.T1, V58.T2, V58.T3, V58.T4, V58.T5, V58.T6
unnamed: LB59.T, LG59.T, LR59.T, V59.T1, V59.T2, V59.T3, V59.T4, V59.T5, V59.T6
unnamed: LB52.T, LG52.T, LR52.T, V52.T1, V52.T2, V52.T3
unnamed: LB51.T, LG51.T, LR51.T, V51.T1, V51.T2, V51.T3, V51.T4, V51.T5, V51.T6
unnamed: LB49.T, LG49.T, LR49.T, V49.T1, V49.T2, V49.T3, V49.T4, V49.T5, V49.T6
unnamed: LB34.T, LG34.T, LR34.T, V34.T1, V34.T2, V34.T3, V34.T4, V34.T5, V34.T6
unnamed: LB45.T, LG45.T, LR45.T, V45.T1, V45.T2, V45.T3, V45.T4, V45.T5, V45.T6
unnamed: LB46.T, LG46.T, LR46.T, V46.T1, V46.T2, V46.T3, V46.T4, V46.T5, V46.T6
unnamed: LB47.T, LG47.T, LR47.T, V47.T1, V47.T2, V47.T3, V47.T4, V47.T5, V47.T6
unnamed: LB37.T, LG37.T, LR37.T, V37.T1, V37.T2, V37.T3, V37.T4, V37.T5, V37.T6
unnamed: LB40.T, LG40.T, LR40.T, V40.T1, V40.T2, V40.T3
unnamed: LB61.T, LG61.T, LR61.T, V61.T1, V61.T2, V61.T3, V61.T4, V61.T5, V61.T6
unnamed: LB62.T, LG62.T, LR62.T, V62.T1, V62.T2, V62.T3, V62.T4, V62.T5, V62.T6
unnamed: LB63.T, LG63.T, LR63.T, V63.T1, V63.T2, V63.T3, V63.T4, V63.T5, V63.T6
unnamed: LB56.T, LG56.T, LR56.T, V56.T1, V56.T2, V56.T3
unnamed: LB55.T, LG55.T, LR55.T, V55.T1, V55.T2, V55.T3, V55.T4, V55.T5, V55.T6
unnamed: LB53.T, LG53.T, LR53.T, V53.T1, V53.T2, V53.T3, V53.T4, V53.T5, V53.T6
unnamed: LB38.T, LG38.T, LR38.T, V38.T1, V38.T2, V38.T3, V38.T4, V38.T5, V38.T6
unnamed: LB13.T, LG13.T, LR13.T, V13.T1, V13.T2, V13.T3, V13.T4, V13.T5, V13.T6
unnamed: LB14.T, LG14.T, LR14.T, V14.T1, V14.T2, V14.T3, V14.T4, V14.T5, V14.T6
unnamed: LB15.T, LG15.T, LR15.T, V15.T1, V15.T2, V15.T3, V15.T4, V15.T5, V15.T6
unnamed: LB5.T, LG5.T, LR5.T, V5.T1, V5.T2, V5.T3, V5.T4, V5.T5, V5.T6
unnamed: LB8.T, LG8.T, LR8.T, V8.T1, V8.T2, V8.T3
unnamed: LB29.T, LG29.T, LR29.T, V29.T1, V29.T2, V29.T3, V29.T4, V29.T5, V29.T6
unnamed: LB30.T, LG30.T, LR30.T, V30.T1, V30.T2, V30.T3, V30.T4, V30.T5, V30.T6
unnamed: LB31.T, LG31.T, LR31.T, V31.T1, V31.T2, V31.T3, V31.T4, V31.T5, V31.T6
unnamed: LB24.T, LG24.T, LR24.T, V24.T1, V24.T2, V24.T3
unnamed: LB23.T, LG23.T, LR23.T, V23.T1, V23.T2, V23.T3, V23.T4, V23.T5, V23.T6
unnamed: LB21.T, LG21.T, LR21.T, V21.T1, V21.T2, V21.T3, V21.T4, V21.T5, V21.T6
unnamed: LB6.T, LG6.T, LR6.T, V6.T1, V6.T2, V6.T3, V6.T4, V6.T5, V6.T6
unnamed: LB2.T, LG2.T, LR2.T, V2.T1, V2.T2, V2.T3, V2.T4, V2.T5, V2.T6
OTMP: M1B.13, U13.5
Q7A: LG21.GC, Q6.7, Q6.8, Q6.8A, Q6.8B, Q6.8C, Q6.8C1, Q6.8C2, Q6.8C3, Q6.78, Q6.78A, Q6.78B
Q7B: LG5.GC, Q6.5, Q6.5A, Q6.5A1, Q6.5B, Q6.5C, Q6.5C1, Q6.5C2, Q6.6, Q6.56, Q6.56A, Q6.56B
Q8A: LR21.GC, Q5.7, Q5.8, Q5.8A, Q5.8B, Q5.8C, Q5.8C1, Q5.8C2, Q5.8C3, Q5.78, Q5.78A, Q5.78B
Q8B: LR5.GC, Q5.5, Q5.5A, Q5.5A1, Q5.5B, Q5.5C, Q5.5C1, Q5.5C2, Q5.6, Q5.56, Q5.56A, Q5.56B
Q9A: LB21.GC, Q3.7, Q3.8, Q3.8A, Q3.8B, Q3.8C, Q3.8C1, Q3.8C2, Q3.8C3, Q3.78, Q3.78A, Q3.78B
Q9B: LB5.GC, Q3.5, Q3.5A, Q3.5A1, Q3.5B, Q3.5C, Q3.5C1, Q3.5C2, Q3.6, Q3.56, Q3.56A, Q3.56B
R1A: LR53.GC, Q4.5, Q4.5A, Q4.5A1, Q4.5B, Q4.5C, Q4.5C1, Q4.5C2, Q4.6, Q4.56, Q4.56A, Q4.56B
R1B: LR37.GC, Q4.7, Q4.8, Q4.8A, Q4.8B, Q4.8C, Q4.8C1, Q4.8C2, Q4.8C3, Q4.78, Q4.78A, Q4.78B
RED: M1A.6, R18.2
RED_LL: U20.4, U21.3
RED_LR: U6.3, U11.4
RED_UL: U15.3, U16.4
RED_UR: U7.3, U10.4
RLLA: LR49.GC, Q11.5, Q11.5A, Q11.5A1, Q11.5B, Q11.5C, Q11.5C1, Q11.5C2, Q11.6, Q11.56, Q11.56A, Q11.56B
RLLB: LR33.GC, Q11.7, Q11.8, Q11.8A, Q11.8B, Q11.8C, Q11.8C1, Q11.8C2, Q11.8C3, Q11.78, Q11.78A, Q11.78B
RULA_1: LR17.GC, Q8.5, Q8.5A, Q8.5A1, Q8.5B, Q8.5C, Q8.5C1, Q8.5C2, Q8.6, Q8.56, Q8.56A, Q8.56B
RULB_1: LR1.GC, Q8.7, Q8.8, Q8.8A, Q8.8B, Q8.8C, Q8.8C1, Q8.8C2, Q8.8C3, Q8.78, Q8.78A, Q8.78B
RX: M1A.2, U8.3, U22.6
RXI: J6.P$2, U22.2
SCLK: M1B.14, U10.7, U11.7, U16.7, U20.7
SYNC: J5.1, R29.1
SYNCIN: M1B.8, R29.2
TH1: LB12.T, LG12.T, LR12.T, V12.T1, V12.T2, V12.T3
TH2: LB3.T, LG3.T, LR3.T, V3.T1, V3.T2, V3.T3, V3.T4, V3.T5, V3.T6
TH3: LB28.T, LG28.T, LR28.T, V28.T1, V28.T2, V28.T3
TH4: LB18.T, LG18.T, LR18.T, V18.T1, V18.T2, V18.T3, V18.T4, V18.T5, V18.T6
TH5: LB35.T, LG35.T, LR35.T, V35.T1, V35.T2, V35.T3, V35.T4, V35.T5, V35.T6
TH6: LB60.T, LG60.T, LR60.T, V60.T1, V60.T2, V60.T3
TH7: LB39.T, LG39.T, LR39.T, V39.T1, V39.T2, V39.T3, V39.T4, V39.T5, V39.T6
TH8: LB64.T, LG64.T, LR64.T, V64.T1, V64.T2, V64.T3
TH9: LB7.T, LG7.T, LR7.T, V7.T1, V7.T2, V7.T3, V7.T4, V7.T5, V7.T6
TH10: LB50.T, LG50.T, LR50.T, V50.T1, V50.T2, V50.T3, V50.T4, V50.T5, V50.T6
TH11: LB54.T, LG54.T, LR54.T, V54.T1, V54.T2, V54.T3, V54.T4, V54.T5, V54.T6
TH12: LB16.T, LG16.T, LR16.T, V16.T1, V16.T2, V16.T3
TH13: LB44.T, LG44.T, LR44.T, V44.T1, V44.T2, V44.T3
TH15: LB48.T, LG48.T, LR48.T, V48.T1, V48.T2, V48.T3
TH16: LB32.T, LG32.T, LR32.T, V32.T1, V32.T2, V32.T3
TH17: LB22.T, LG22.T, LR22.T, V22.T1, V22.T2, V22.T3, V22.T4, V22.T5, V22.T6
TRIG: M1A.5, U2.2
TX: M1A.3, U8.1
TXRX: J4.P$2, U8.4
UL_EN: M1B.9, U16.6
UR_EN: M1B.11, U10.6
VUSB: D1.K, M1B.1
V_IR: C13.1, C17.1, C41.1, C54.1, D2.K, D3.K, D4.K, D5.K, R23.2, R26.2, R49.2, R69.2, SH1.1, U9.4, U12.4, U18.4, U24.4
V_RGB: C1.1, C2.1, C3.1, C4.1, C14.1, C16.1, C20.+, C21.+, C32.1, C34.1, C39.1, C42.1, C43.+, C48.1, C50.1, J1.1A, J1.1B, LB9.GA, LB13.GA, LB25.GA, LB29.GA, LB41.GA, LB45.GA, LB57.GA, LB61.GA, LG9.GA, LG13.GA, LG25.GA, LG29.GA, LG41.GA, LG45.GA, LG57.GA, LG61.GA, LR9.GA, LR13.GA, LR25.GA, LR29.GA, LR41.GA, LR45.GA, LR57.GA, LR61.GA, PS1.1, R13.2, R14.2, R15.2, R16.2, R20.2, R21.2, R34.2, R37.2, R47.2, R54.2, R58.2, R67.2, SH1.2
